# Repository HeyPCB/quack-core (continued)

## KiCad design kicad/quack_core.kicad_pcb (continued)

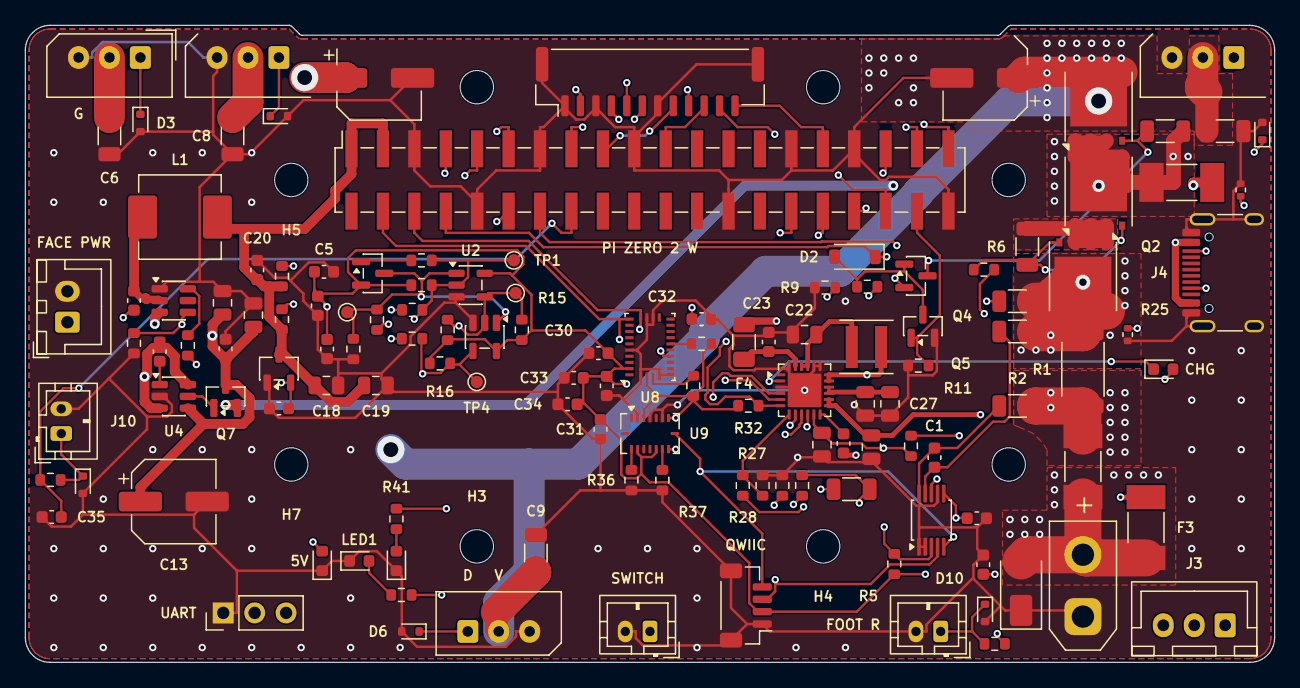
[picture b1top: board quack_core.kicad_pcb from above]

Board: 4 copper layers, 101.0 x 51.5 mm, 138 parts (0 on the bottom side), 78 nets.

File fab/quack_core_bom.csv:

"Reference","Value","Footprint","MPN","LCSC","Qty"
"C1,C2,C3,C4,C12,C16,C17,C29,C30,C35,C36","100nF","Capacitor_SMD:C_0603_1608Metric","CC0603KRX7R9BB104","C14663","11"
"C5,C20,C21,C22,C32","1uF","Capacitor_SMD:C_0603_1608Metric","CL10A105KB8NNNC","C15849","5"
"C6,C7,C8,C9","10uF","Capacitor_SMD:C_1206_3216Metric","CL31A106KBHNNNE","C13585","4"
"C10,C11,C13","470uF 16V","Capacitor_SMD:CP_Elec_6.3x7.7","RVT1C471M0607","C2977552","3"
"C14,C15,C28","10uF","Capacitor_SMD:C_0805_2012Metric","CL21A106KAYNNNE","C15850","3"
"C18,C19,C23,C26,C27","22uF","Capacitor_SMD:C_0805_2012Metric","CL21A226MAQNNNE","C45783","5"
"C24","47nF","Capacitor_SMD:C_0603_1608Metric","CL10B473KB8NNNC","C1622","1"
"C25","4.7uF","Capacitor_SMD:C_0805_2012Metric","CL21A475KAQNNNE","C1779","1"
"C31","22nF","Capacitor_SMD:C_0603_1608Metric","CL10B223KB8NNNC","C21122","1"
"D1","SMAJ10CA","Diode_SMD:D_SMA","SMAJ10CA","C19077530","1"
"D2","B5819W","Diode_SMD:D_SOD-123","B5819W SL","C8598","1"
"D3,D4,D5,D6,D9,D10","ESD5Z5.0","Diode_SMD:D_SOD-523","ESD5Z5.0T1G","C82044","6"
"D7","Green (5V)","LED_SMD:LED_0603_1608Metric","KT-0603G","C12624","1"
"D8","Orange (CHG)","LED_SMD:LED_0603_1608Metric","XL-1608UOC-06","C965800","1"
"D11","Red (LED1)","LED_SMD:LED_0603_1608Metric","KT-0603R","C2286","1"
"D12","Red (LED2)","LED_SMD:LED_0603_1608Metric","KT-0603R","C2286","1"
"F1","20A","Fuse:Fuse_Littelfuse-NANO2-451_453","0451020.MRL","C178980","1"
"F2,F3","5A","Fuse:Fuse_Littelfuse-NANO2-451_453","0451005.MRL","C48467","2"
"F4","2A PTC","Fuse:Fuse_1206_3216Metric","1206L200/16NR","C22374899","1"
"J1","Pi Zero 2 W","Connector_PinSocket_2.54mm:PinSocket_2x20_P2.54mm_Vertical_SMD","PM254-2-20-S-8.5","C3975165","1"
"J2","XT30 BATT","Connector_AMASS:AMASS_XT30UPB-M_1x02_P5.0mm_Vertical","XT30UPB-M","C428721","1"
"J3","BALANCE","Connector_JST:JST_XH_B3B-XH-A_1x03_P2.50mm_Vertical","B3B-XH-A(LF)(SN)","C144394","1"
"J4","USB-C CHARGE","Connector_USB:USB_C_Receptacle_HRO_TYPE-C-31-M-12","TYPE-C-31-M-12","C165948","1"
"J5","SWITCH","Connector_JST:JST_PH_B2B-PH-K_1x02_P2.00mm_Vertical","B2B-PH-K-S(LF)(SN)","C131337","1"
"J6,J7,J8,J9","SERVO","Connector_Molex:Molex_SPOX_5267-03A_1x03_P2.50mm_Vertical","HC-5264-3A","C2845815","4"
"J10,J11","FOOT","Connector_JST:JST_PH_B2B-PH-K_1x02_P2.00mm_Vertical","B2B-PH-K-S(LF)(SN)","C131337","2"
"J12","FACE","Connector_JST:JST_GH_BM12B-GHS-TBT_1x12-1MP_P1.25mm_Vertical","BM12B-GHS-TBT(LF)(SN)(N)","C2983891","1"
"J13","FACE PWR","Connector_JST:JST_XH_B2B-XH-A_1x02_P2.50mm_Vertical","B2B-XH-A(LF)(SN)","C158012","1"
"J14","QWIIC","Connector_JST:JST_SH_BM04B-SRSS-TB_1x04-1MP_P1.00mm_Vertical","BM04B-SRSS-TB(LF)(SN)","C160390","1"
"J16","UART","Connector_PinHeader_2.54mm:PinHeader_1x03_P2.54mm_Vertical","PZ254V-11-03P","C2937625","1"
"L1","5.6uH","Inductor_SMD:L_Changjiang_FXL0630","FXL0630-5R6-M","C475914","1"
"L2","1uH","Inductor_SMD:L_Coilcraft_XxL4020","XFL4020-102MEC","C5355380","1"
"Q1,Q2,Q3","AON6411","Package_DFN_QFN:AO_DFN-8-1EP_5.55x5.2mm_P1.27mm_EP4.12x4.6mm","AON6411","C81007","3"
"Q4,Q5,Q7","AO3400A","Package_TO_SOT_SMD:SOT-23","AO3400A","C20917","3"
"Q6","MMBT3906","Package_TO_SOT_SMD:SOT-23","MMBT3906LT1G","C53444","1"
"R1","1mΩ 3W","Resistor_SMD:R_2512_6332Metric","HoJLR2512-3W-1mR-1%","C2903470","1"
"R2,R3,R4","10","Resistor_SMD:R_1206_3216Metric","1206W4F100JT5E","C17903","3"
"R5,R7,R9,R12,R13,R15,R16,R23,R28,R32,R34,R35","10k","Resistor_SMD:R_0603_1608Metric","FRC0603F1002TS","C2906982","12"
"R6,R8","100k","Resistor_SMD:R_1206_3216Metric","1206W4F1003T5E","C17900","2"
"R10,R11","100k","Resistor_SMD:R_0603_1608Metric","0603WAF1003T5E","C25803","2"
"R14","20k","Resistor_SMD:R_0603_1608Metric","0603WAF2002T5E","C4184","1"
"R17,R18","0","Resistor_SMD:R_0603_1608Metric","0603WAF0000T5E","C21189","2"
"R21","33","Resistor_SMD:R_0603_1608Metric","0603WAF330JT5E","C23140","1"
"R22","53.6k","Resistor_SMD:R_0603_1608Metric","FRC0603F5362TS","C2930115","1"
"R24,R33","2.2k","Resistor_SMD:R_0603_1608Metric","0603WAF2201T5E","C4190","2"
"R25,R26","5.1k","Resistor_SMD:R_0402_1005Metric","0402WGF5101TCE","C25905","2"
"R27","750","Resistor_SMD:R_0603_1608Metric","0603WAF7500T5E","C23241","1"
"R29","12.4k","Resistor_SMD:R_0603_1608Metric","FRC0603F1242TS","C2930060","1"
"R30","330","Resistor_SMD:R_0603_1608Metric","0603WAF3300T5E","C23138","1"
"R31","100","Resistor_SMD:R_1206_3216Metric","1206W4F1000T5E","C17901","1"
"R38,R39,R40,R41","1k","Resistor_SMD:R_0603_1608Metric","0603WAF1001T5E","C21190","4"
"U1","INA226","Package_SO:TSSOP-10_3x3mm_P0.5mm","INA226AIDGSR","C49851","1"
"U2","74LVC1G126","Package_TO_SOT_SMD:SOT-23-5","SN74LVC1G126DBVR","C7834","1"
"U3","74LVC1G125","Package_TO_SOT_SMD:SOT-23-5","SN74LVC1G125DBVR","C23654","1"
"U4","LM74700-Q1","Package_TO_SOT_SMD:SOT-23-6","LM74700QDBVRQ1","C2941042","1"
"U5","TPS56339","Package_TO_SOT_SMD:SOT-23-6","TPS56339DDCR","C2071106","1"
"U6","XC6206P332","Package_TO_SOT_SMD:SOT-23-3","XC6206P332MR-G","C5446","1"
"U7","BQ25887","Package_DFN_QFN:Texas_RGE0024H_VQFN-24-1EP_4x4mm_P0.5mm_EP2.7x2.7mm","BQ25887RGER","C2761614","1"
"U8","BNO055","Package_LGA:LGA-28_5.2x3.8mm_P0.5mm","BNO055","C93216","1"
